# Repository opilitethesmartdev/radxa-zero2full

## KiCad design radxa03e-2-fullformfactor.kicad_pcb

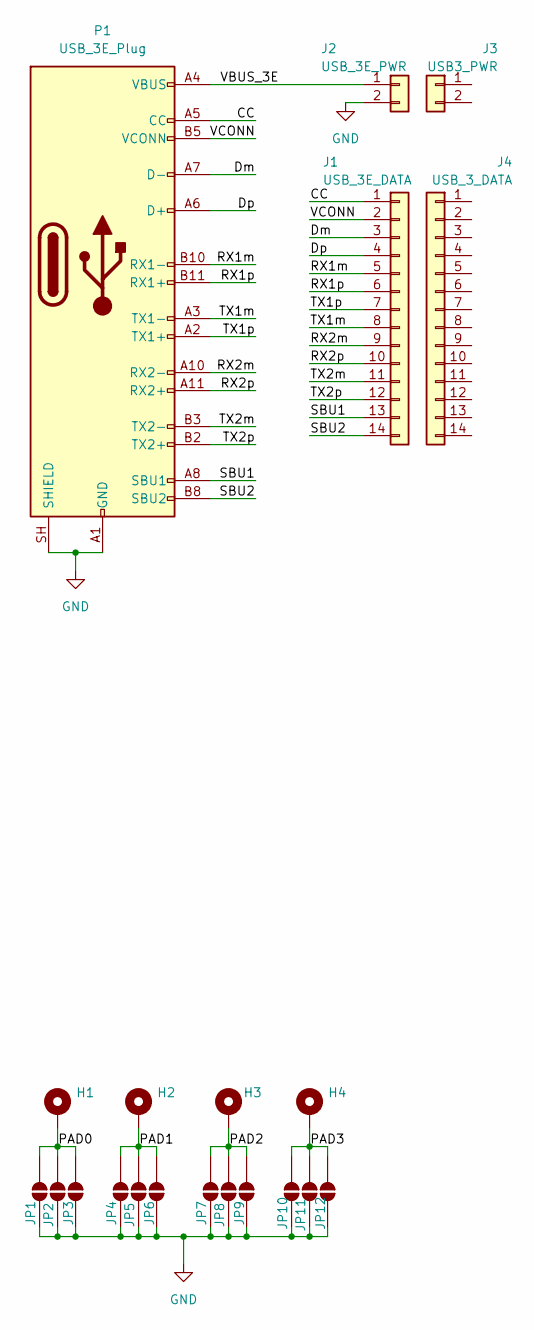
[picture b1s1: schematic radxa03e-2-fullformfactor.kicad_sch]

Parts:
H1, H2, H3, H4: MountingHole_Pad; MountingHole_2.7mm_M2.5_DIN965_Pad
J1: USB_3E_DATA; Amphenol_F32R-1A7x1-11014_1x14-1MP_P0.5mm_Horizontal
J2: USB_3E_PWR; JST_ZH_B2B-ZR_1x02_P1.50mm_Vertical
J3: USB3_PWR; JST_ZH_B2B-ZR_1x02_P1.50mm_Vertical
J4: USB_3_DATA; Amphenol_F32R-1A7x1-11014_1x14-1MP_P0.5mm_Horizontal
JP1, JP2, JP3, JP4, JP5, JP6, JP7, JP8, JP9, JP10, JP11, JP12: SolderJumper_2_Open; SolderJumper-2_P1.3mm_Open_RoundedPad1.0x1.5mm
P1: USB_3E_Plug; USB_C_Plug_Molex_105444

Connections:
/CC: J1.1, P1.A5 (CC)
/Dm: J1.3, P1.A7 (D-)
/Dp: J1.4, P1.A6 (D+)
/PAD0: H1.1 (1_1), JP1.2 (B), JP2.2 (B), JP3.2 (B)
/PAD1: H2.1 (1_1), JP4.2 (B), JP5.2 (B), JP6.2 (B)
/PAD2: H3.1 (1_1), JP7.2 (B), JP8.2 (B), JP9.2 (B)
/PAD3: H4.1 (1_1), JP10.2 (B), JP11.2 (B), JP12.2 (B)
/RX1m: J1.5, P1.B10 (RX1-)
/RX1p: J1.6, P1.B11 (RX1+)
/RX2m: J1.9, P1.A10 (RX2-)
/RX2p: J1.10, P1.A11 (RX2+)
/SBU1: J1.13, P1.A8 (SBU1)
/SBU2: J1.14, P1.B8 (SBU2)
/TX1m: J1.8, P1.A3 (TX1-)
/TX1p: J1.7, P1.A2 (TX1+)
/TX2m: J1.11, P1.B3 (TX2-)
/TX2p: J1.12, P1.B2 (TX2+)
/VBUS_3E: J2.1, P1.A4 (VBUS), P1.A9 (VBUS), P1.B4 (VBUS), P1.B9 (VBUS)
/VCONN: J1.2, P1.B5 (VCONN)
GND: J2.2, JP1.1 (A), JP2.1 (A), JP3.1 (A), JP4.1 (A), JP5.1 (A), JP6.1 (A), JP7.1 (A), JP8.1 (A), JP9.1 (A), JP10.1 (A), JP11.1 (A), JP12.1 (A), P1.A1 (GND), P1.A12 (GND), P1.B1 (GND), P1.B12 (GND), P1.SH (SHIELD)

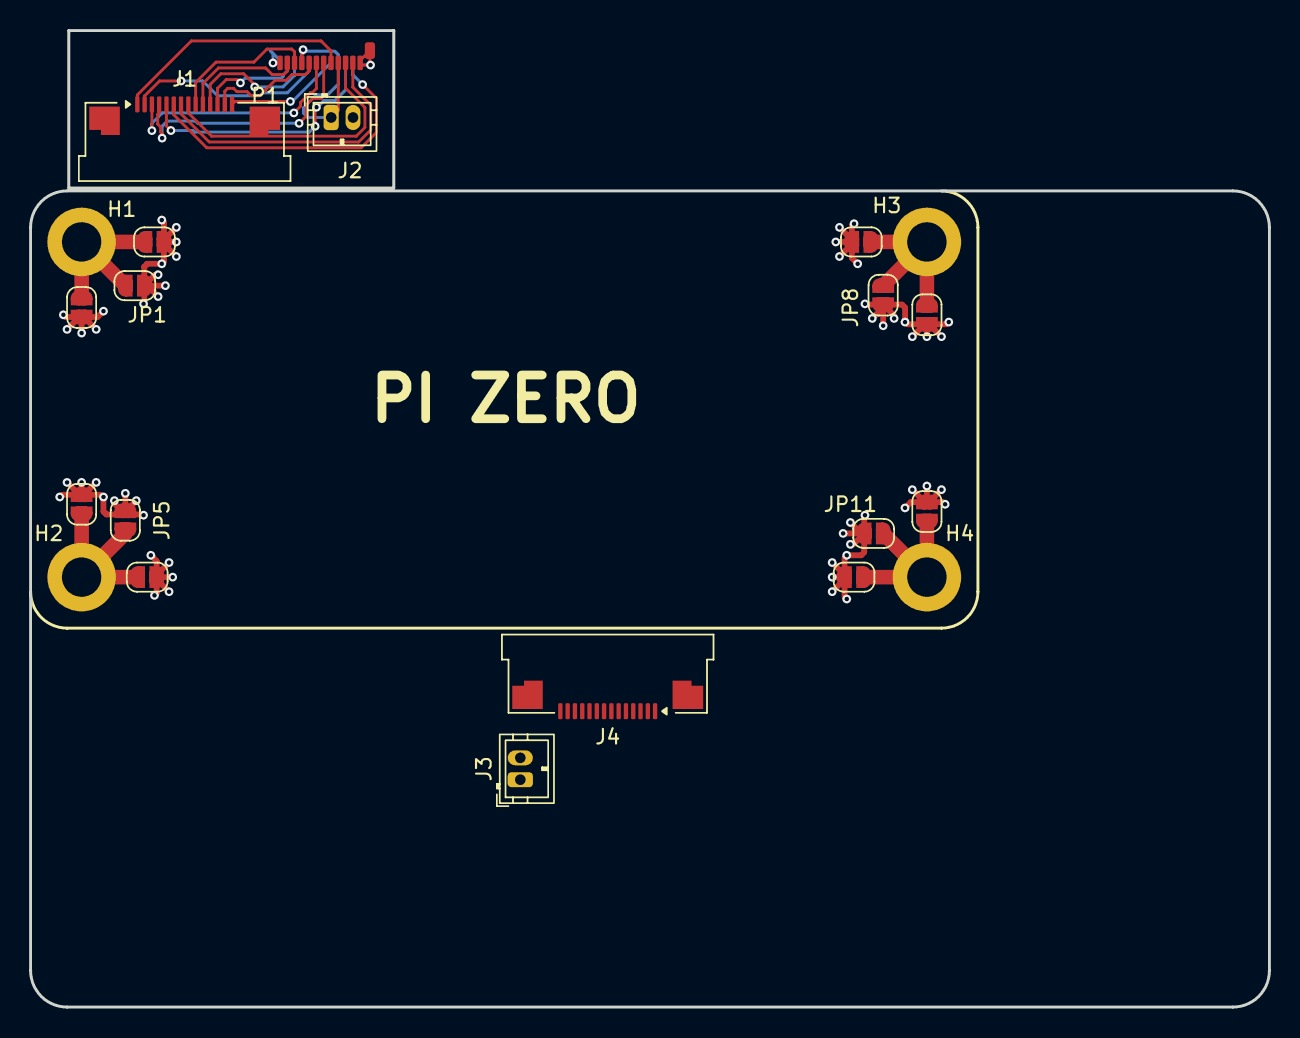
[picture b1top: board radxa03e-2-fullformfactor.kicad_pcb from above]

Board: 2 copper layers, 85.0 x 56.0 mm, 21 parts (0 on the bottom side), 20 nets.
